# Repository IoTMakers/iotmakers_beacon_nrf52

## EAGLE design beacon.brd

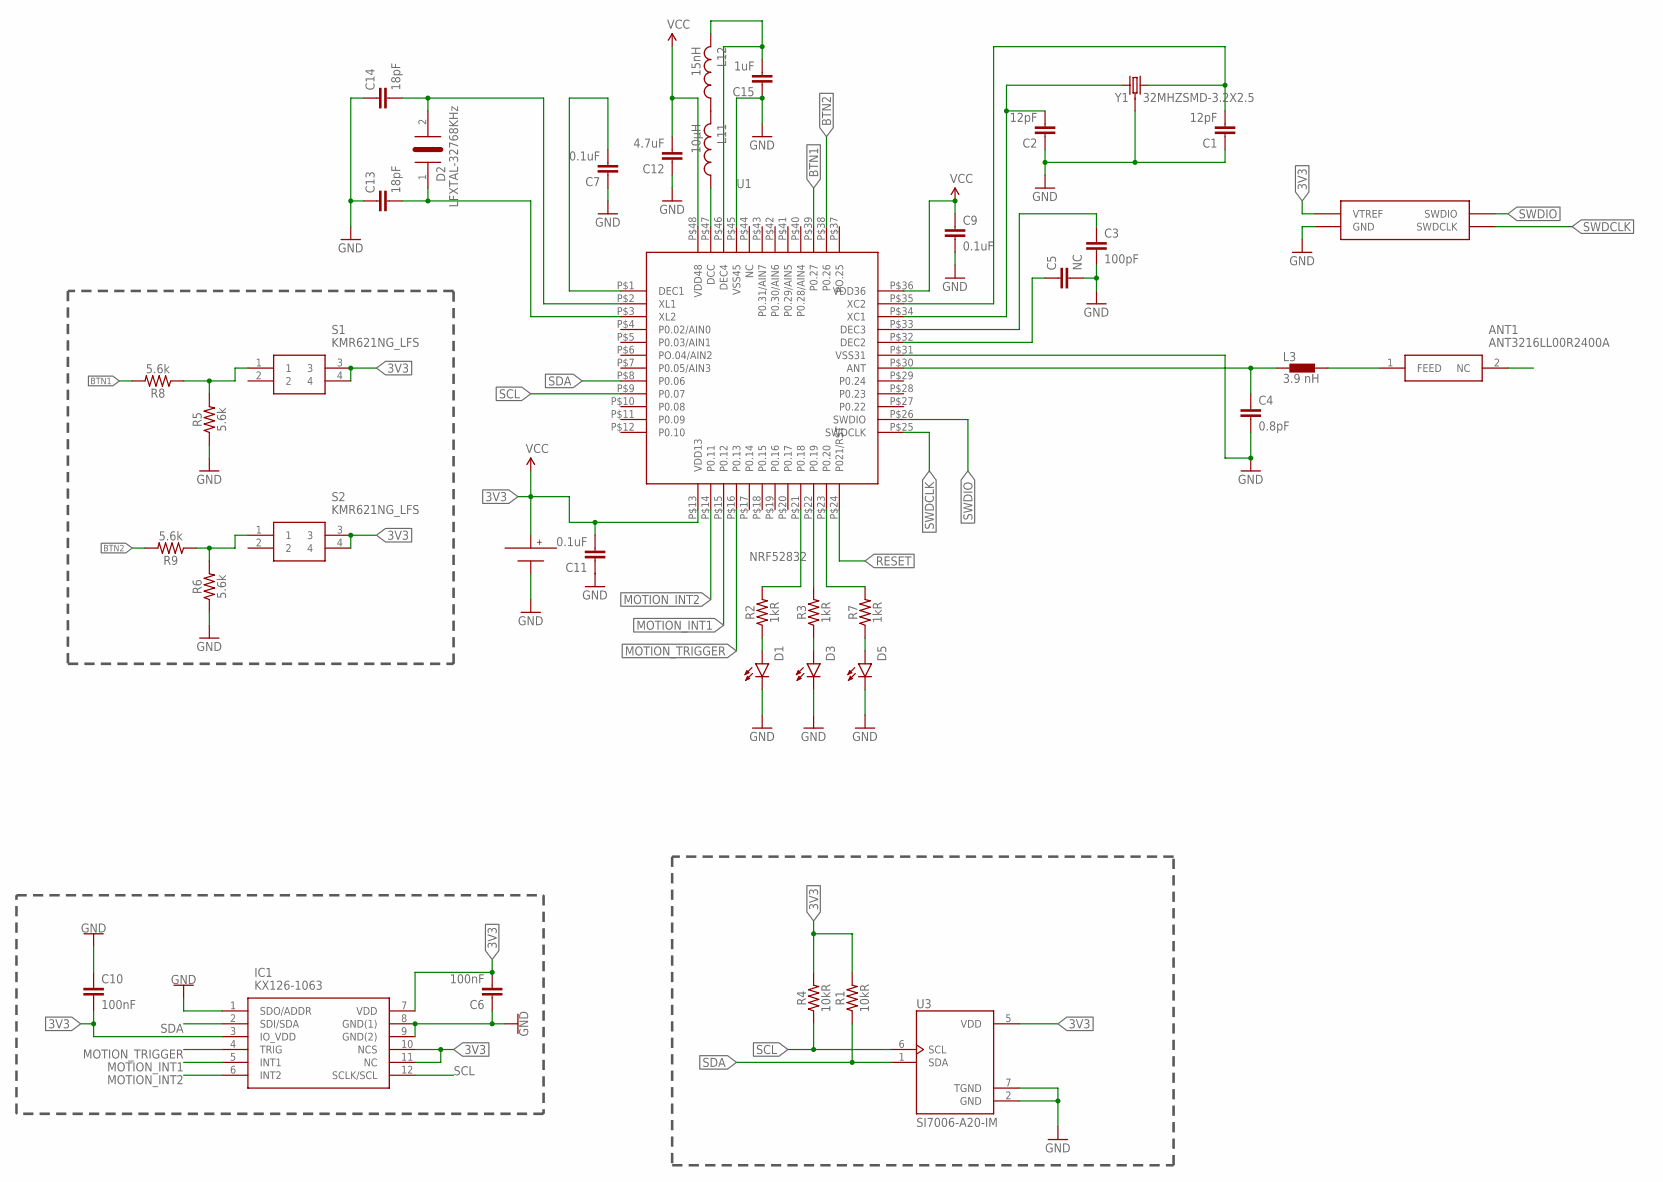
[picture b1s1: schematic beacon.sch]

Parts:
ANT1: ANT3216LL00R2400A; ANTC3216X135N
C1, C2: 12pF; 0603
C3: 100pF; 0603
C4: 0.8pF; 0603
C5: NC; 0603
C6, C10: 100nF; 0603
C7, C9, C11: 0.1uF; 0603
C12: 4.7uF; 0603
C13, C14: 18pF; 0603
C15: 1uF; 0603
D1, D3, D5: LED0603; LED-0603
D2: LFXTAL-32768KHz; DIOC3215X90N
IC1: KX126-1063; 2X2X0.9MMLGA
J1: JTAG-PROGJTAG_SMALL; JTAG_PROG_SMALL
L3: 3.9 nH; 0402
L11: 10µH; RESC0603_N
L12: 15nH; RESC0402_N
R1, R4: 10kR; 0603
R2, R3, R7: 1kR; 0603
R5, R6, R8, R9: 5.6k; 0603
S1, S2: KMR621NG_LFS; KMR621NG
U1: NRF52832; QFN-48
U3: SI7006-A20-IM; SON100P300X300X80-7N
U$1: BAT-HLD-001
Y1: 32MHZSMD-3.2X2.5; CRYSTAL-SMD-3.2X2.5MM

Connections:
3V3: C6.2, C9.1, C10.2, C11.2, C12.2, IC1.3 (IO_VDD), IC1.7 (VDD), IC1.10 (NCS), IC1.11 (NC), J1.VREF (VTREF), R1.2, R4.2, S1.3, S1.4, S2.3, S2.4, U1.P$13 (VDD13), U1.P$36 (VDD36), U1.P$48 (VDD48), U3.5 (VDD), U$1.+@1 (+), U$1.+@2 (+)
BTN1: R8.2, U1.P$39 (P0.27)
BTN2: R9.2, U1.P$38 (P0.26)
DEC4: C15.2, L12.2, U1.P$46 (DEC4)
GND: C1.1, C2.1, C3.2, C4.2, C5.2, C6.1, C7.1, C9.2, C10.1, C11.1, C12.1, C13.1, C14.1, C15.1, D1.C, D3.C, D5.C, IC1.1 (SDO/ADDR), IC1.8 (GND(1)), IC1.9 (GND(2)), J1.GND, R5.1, R6.1, U1.P$31 (VSS31), U1.P$45 (VSS45), U3.2 (GND), U3.7 (TGND), U$1.-, Y1.2 (3), Y1.4 (3)
MOTION_INT1: IC1.5 (INT1), U1.P$15 (P0.12)
MOTION_INT2: IC1.6 (INT2), U1.P$14 (P0.11)
MOTION_TRIGGER: IC1.4 (TRIG), U1.P$16 (P0.13)
unnamed: ANT1.1 (FEED), L3.2
unnamed: C2.2, U1.P$34 (XC1), Y1.1
unnamed: C4.1, L3.1, U1.P$30 (ANT)
unnamed: C14.2, D2.2 (A), U1.P$2 (XL1)
unnamed: R7.2, U1.P$23 (P0.20)
unnamed: R3.2, U1.P$22 (P0.19)
unnamed: R2.2, U1.P$21 (P0.18)
unnamed: C13.2, D2.1 (K), U1.P$3 (XL2)
unnamed: C1.2, U1.P$35 (XC2), Y1.3 (2)
unnamed: R5.2, R8.1, S1.1
unnamed: C7.2, U1.P$1 (DEC1)
unnamed: R6.2, R9.1, S2.1
unnamed: D1.A, R2.1
unnamed: D3.A, R3.1
unnamed: D5.A, R7.1
unnamed: L11.2, L12.1
unnamed: C3.1, U1.P$33 (DEC3)
unnamed: L11.1, U1.P$47 (DCC)
unnamed: C5.1, U1.P$32 (DEC2)
RESET: U1.P$24 (P021/RST)
SCL: IC1.12 (SCLK/SCL), R4.1, U1.P$9 (P0.07), U3.6 (SCL)
SDA: IC1.2 (SDI/SDA), R1.1, U1.P$8 (P0.06), U3.1 (SDA)
SWDCLK: J1.SCK (SWDCLK), U1.P$25 (SWDCLK)
SWDIO: J1.DIO (SWDIO), U1.P$26 (SWDIO)

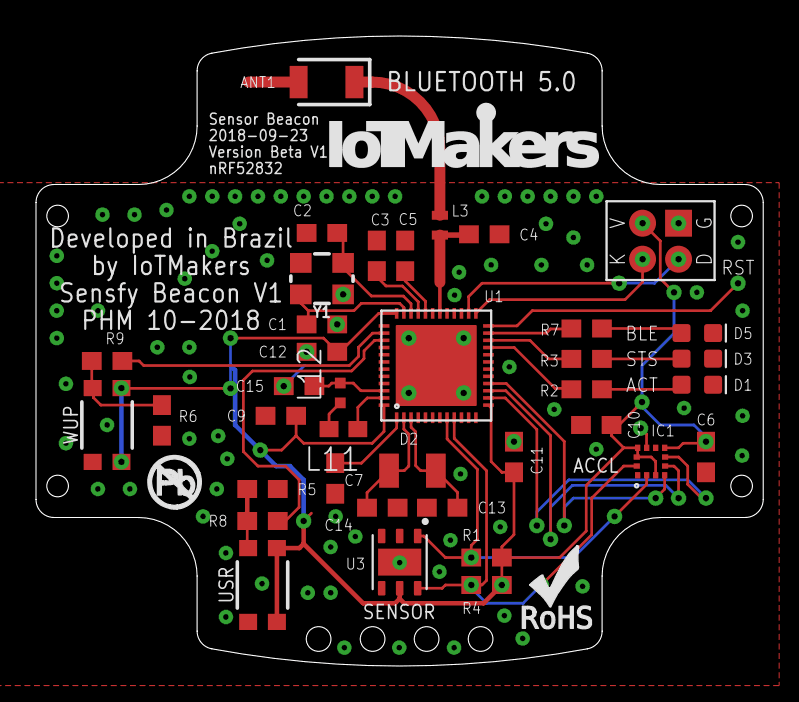
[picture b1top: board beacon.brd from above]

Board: 2 copper layers, 40.4 x 35.0 mm, 42 parts (1 on the bottom side), 31 nets.

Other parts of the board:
U$2: LOGO_L
U$3: NO_PB_LOGO_0.120
U$4: ROHS_LOGO_0.18_IN

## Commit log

2020-08-05 Files added

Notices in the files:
parts and their libraries:
SparkFun-LED: Licensing: Creative Commons ShareAlike 4.0 International - https://creativecommons.org/licenses/by-sa/4.0
